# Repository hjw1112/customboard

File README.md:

# Customboard!

This is a custom built mechanical keyboard. Everything except switches and keycaps are custom built including pcb and case!

I always wanted to get a mechanical keyboard but It was to expensive to get. But, I learnt how to make simple macropad by hack club event "hackpad" and started working on this. Also, I liked the idea because everything was customizable including silkscreen on PCB and every behavior of keyboard.

You can work on the same project or benchmark this if you want to. I have all source file or link to source file of the project in this repo :)

### PCB

### Schematic

### Case

---
### BOM

# Custom Keyboard BOM (Bill of Materials)

| Component                    | Price (USD) | Price (EUR) | Source     |
|------------------------------|-------------|-------------|------------|
| Nice!nano compatible board   | $4.86       | €4.26       | Aliexpress |
| Kailh hotswap sockets        | $8.52       | €7.47       | Aliexpress |
| Akko V3 Pro Cream Switches   | $33.21      | €29.13      | Aliexpress |
| 0.91 inch OLED               | $1.01       | €0.89       | Aliexpress |
| TCA9555 expansion board      | $3.52       | €3.09       | Aliexpress |
| Stabilizers                  | $11.92      | €10.46      | Aliexpress |
| EC11 encoder                 | $5.07       | €4.45       | Aliexpress |
| 1N4148 Diodes                | $1.45       | €1.27       | Aliexpress |
| 0603 SMD 1000nF capacitor    | $1.36       | €1.19       | Aliexpress |
| 0603 SMD 4.7k resistor       | $1.12       | €0.98       | Aliexpress |
| M2.5 heatset insert          | $2.44       | €2.14       | Aliexpress |
| M2.5 screws                  | $5.48       | €4.81       | Aliexpress |
| Foam                         | $6.48       | €5.68       | Aliexpress |
| Keycaps                      | $16.89      | €14.82      | Aliexpress |
| Standoff                     | $3.23       | €2.83       | Aliexpress |
| Battery                      | $6.50       | €5.70       | Aliexpress |
| JST PH2.0 male connector     | $1.87       | €1.64       | Aliexpress |
| Cable                        | $11.92      | €10.46      | Aliexpress |
| PCB                          | $19.80      |             | JLC PCB    |

---

**Total: $146.65**

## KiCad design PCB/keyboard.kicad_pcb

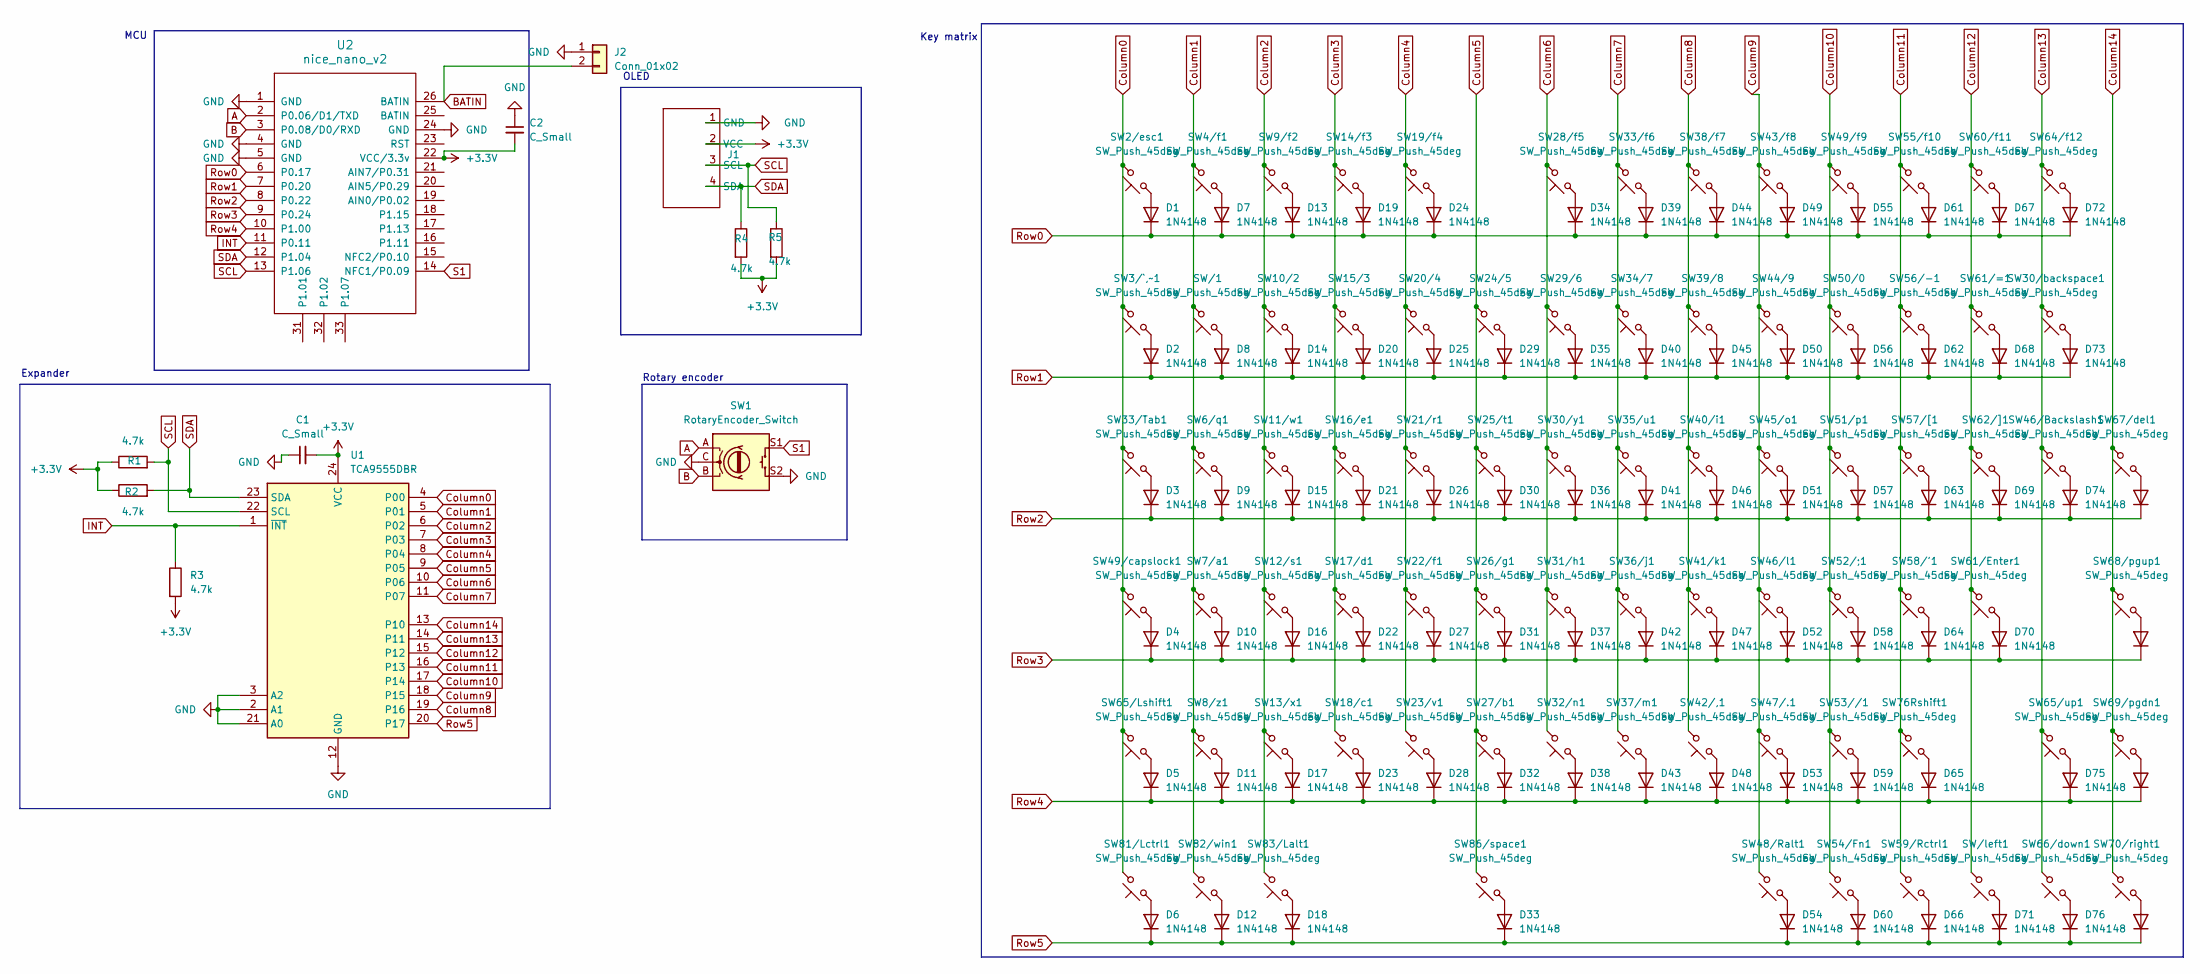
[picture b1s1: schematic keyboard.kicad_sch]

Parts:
C1, C2: C_Small; C_0603_1608Metric_Pad1.08x0.95mm_HandSolder
D1, D2, D3, D4, D5, D6, D7, D8, D9, D10, D11, D12, D13, D14, D15, D16, D17, D18, D19, D20, D21, D22, D23, D24, D25, D26, D27, D28, D29, D30, D31, D32, D33, D34, D35, D36, D37, D38, D39, D40, D41, D42, D43, D44, D45, D46, D47, D48, D49, D50, D51, D52, D53, D54, D55, D56, D57, D58, D59, D60, D61, D62, D63, D64, D65, D66, D67, D68, D69, D70, D71, D72, D73, D74, D75, D76, D77, D78, D79, D80: 1N4148; D_DO-35_SOD27_P7.62mm_Horizontal
J1: SSD1306-0.91-OLED-4pin-128x32
J2: Conn_01x02; JST_PH_S2B-PH-K_1x02_P2.00mm_Horizontal
R1, R2, R3, R4, R5: 4.7k; R_0603_1608Metric_Pad0.98x0.95mm_HandSolder
SW1: RotaryEncoder_Switch; RotaryEncoder_Alps_EC11E-Switch_Vertical_H20mm_MountingHoles
SW2/esc1, SW3/`,~1, SW4/f1, SW6/q1, SW7/a1, SW8/z1, SW9/f2, SW10/2, SW11/w1, SW12/s1, SW13/x1, SW14/f3, SW15/3, SW16/e1, SW17/d1, SW18/c1, SW19/f4, SW20/4, SW21/r1, SW22/f1, SW23/v1, SW24/5, SW25/t1, SW26/g1, SW27/b1, SW28/f5, SW29/6, SW30/y1, SW31/h1, SW32/n1, SW33/f6, SW34/7, SW35/u1, SW36/j1, SW37/m1, SW38/f7, SW39/8, SW40/i1, SW41/k1, SW42/,1, SW43/f8, SW44/9, SW45/o1, SW46/l1, SW47/.1, SW48/Ralt1, SW49/f9, SW50/0, SW51/p1, SW52/;1, SW53//1, SW54/Fn1, SW55/f10, SW56/-1, SW57/[1, SW58/'1, SW59/Rctrl1, SW60/f11, SW61/=1, SW62/]1, SW64/f12, SW65/up1, SW66/down1, SW67/del1, SW68/pgup1, SW69/pgdn1, SW70/right1: SW_Push_45deg; CherryMX_1.00u_KailhSocket
SW30/backspace1: SW_Push_45deg; CherryMX_2.00u_KailhSocket_StabWireBottom
SW33/Tab1, SW46/Backslash1: SW_Push_45deg; CherryMX_1.50u_KailhSocket
SW49/capslock1, SW76Rshift1: SW_Push_45deg; CherryMX_1.75u_KailhSocket
SW61/Enter1, SW65/Lshift1: SW_Push_45deg; CherryMX_2.25u_KailhSocket_StabWireBottom
SW81/Lctrl1, SW82/win1, SW83/Lalt1: SW_Push_45deg; CherryMX_1.25u_KailhSocket
SW86/space1: SW_Push_45deg; CherryMX_6.25u_KailhSocket_StabWireBottom
SW/1: SW_Push_45deg; CherryMX_1.00u_KailhSocket
SW/left1: SW_Push_45deg; CherryMX_1.00u_KailhSocket
U1: TCA9555DBR; SSOP-24_5.3x8.2mm_P0.65mm
U2: nice_nano_v2; nice nano v2 final

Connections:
+3.3V: C1.2, C2.2, J1.2 (VCC), R1.1, R2.1, R3.2, R4.2, R5.2, U1.24 (VCC), U2.22 (VCC/3.3v)
A: SW1.A, U2.2 (P0.06/D1/TXD)
B: SW1.B, U2.3 (P0.08/D0/RXD)
BATIN: J2.2, U2.26 (BATIN)
Column0: SW2/esc1.2, SW3/`,~1.2, SW33/Tab1.2, SW49/capslock1.2, SW65/Lshift1.2, SW81/Lctrl1.2, U1.4 (P00)
Column1: SW4/f1.2, SW6/q1.2, SW7/a1.2, SW8/z1.2, SW82/win1.2, SW/1.2, U1.5 (P01)
Column2: SW9/f2.2, SW10/2.2, SW11/w1.2, SW12/s1.2, SW13/x1.2, SW83/Lalt1.2, U1.6 (P02)
Column3: SW14/f3.2, SW15/3.2, SW16/e1.2, SW17/d1.2, SW18/c1.2, U1.7 (P03)
Column4: SW19/f4.2, SW20/4.2, SW21/r1.2, SW22/f1.2, SW23/v1.2, U1.8 (P04)
Column5: SW24/5.2, SW25/t1.2, SW26/g1.2, SW27/b1.2, SW86/space1.2, U1.9 (P05)
Column6: SW28/f5.2, SW29/6.2, SW30/y1.2, SW31/h1.2, SW32/n1.2, U1.10 (P06)
Column7: SW33/f6.2, SW34/7.2, SW35/u1.2, SW36/j1.2, SW37/m1.2, U1.11 (P07)
Column8: SW38/f7.2, SW39/8.2, SW40/i1.2, SW41/k1.2, SW42/,1.2, U1.19 (P16)
Column9: SW43/f8.2, SW44/9.2, SW45/o1.2, SW46/l1.2, SW47/.1.2, SW48/Ralt1.2, U1.18 (P15)
Column10: SW49/f9.2, SW50/0.2, SW51/p1.2, SW52/;1.2, SW53//1.2, SW54/Fn1.2, U1.17 (P14)
Column11: SW55/f10.2, SW56/-1.2, SW57/[1.2, SW58/'1.2, SW59/Rctrl1.2, SW76Rshift1.2, U1.16 (P13)
Column12: SW60/f11.2, SW61/=1.2, SW61/Enter1.2, SW62/]1.2, SW/left1.2, U1.15 (P12)
Column13: SW30/backspace1.2, SW46/Backslash1.2, SW64/f12.2, SW65/up1.2, SW66/down1.2, U1.14 (P11)
Column14: SW67/del1.2, SW68/pgup1.2, SW69/pgdn1.2, SW70/right1.2, U1.13 (P10)
GND: C1.1, C2.1, J1.1 (GND), J2.1, SW1.C, SW1.S2, U1.2 (A1), U1.3 (A2), U1.12 (GND), U1.21 (A0), U2.1 (GND), U2.4 (GND), U2.5 (GND), U2.24 (GND)
INT: R3.1, U1.1 (~INT), U2.11 (P0.11)
unnamed: D1.2 (A), SW2/esc1.1
unnamed: D2.2 (A), SW3/`,~1.1
unnamed: D3.2 (A), SW33/Tab1.1
unnamed: D4.2 (A), SW49/capslock1.1
unnamed: D5.2 (A), SW65/Lshift1.1
unnamed: D6.2 (A), SW81/Lctrl1.1
unnamed: D7.2 (A), SW4/f1.1
unnamed: D8.2 (A), SW/1.1
unnamed: D9.2 (A), SW6/q1.1
unnamed: D10.2 (A), SW7/a1.1
unnamed: D11.2 (A), SW8/z1.1
unnamed: D12.2 (A), SW82/win1.1
unnamed: D13.2 (A), SW9/f2.1
unnamed: D14.2 (A), SW10/2.1
unnamed: D15.2 (A), SW11/w1.1
unnamed: D16.2 (A), SW12/s1.1
unnamed: D17.2 (A), SW13/x1.1
unnamed: D18.2 (A), SW83/Lalt1.1
unnamed: D19.2 (A), SW14/f3.1
unnamed: D20.2 (A), SW15/3.1
unnamed: D21.2 (A), SW16/e1.1
unnamed: D22.2 (A), SW17/d1.1
unnamed: D23.2 (A), SW18/c1.1
unnamed: D24.2 (A), SW19/f4.1
unnamed: D25.2 (A), SW20/4.1
unnamed: D26.2 (A), SW21/r1.1
unnamed: D27.2 (A), SW22/f1.1
unnamed: D28.2 (A), SW23/v1.1
unnamed: D29.2 (A), SW24/5.1
unnamed: D30.2 (A), SW25/t1.1
unnamed: D31.2 (A), SW26/g1.1
unnamed: D32.2 (A), SW27/b1.1
unnamed: D33.2 (A), SW86/space1.1
unnamed: D34.2 (A), SW28/f5.1
unnamed: D35.2 (A), SW29/6.1
unnamed: D36.2 (A), SW30/y1.1
unnamed: D37.2 (A), SW31/h1.1
unnamed: D38.2 (A), SW32/n1.1
unnamed: D39.2 (A), SW33/f6.1
unnamed: D40.2 (A), SW34/7.1
unnamed: D41.2 (A), SW35/u1.1
unnamed: D42.2 (A), SW36/j1.1
unnamed: D43.2 (A), SW37/m1.1
unnamed: D44.2 (A), SW38/f7.1
unnamed: D45.2 (A), SW39/8.1
unnamed: D46.2 (A), SW40/i1.1
unnamed: D47.2 (A), SW41/k1.1
unnamed: D48.2 (A), SW42/,1.1
unnamed: D49.2 (A), SW43/f8.1
unnamed: D50.2 (A), SW44/9.1
unnamed: D51.2 (A), SW45/o1.1
unnamed: D52.2 (A), SW46/l1.1
unnamed: D53.2 (A), SW47/.1.1
unnamed: D54.2 (A), SW48/Ralt1.1
unnamed: D55.2 (A), SW49/f9.1
unnamed: D56.2 (A), SW50/0.1
unnamed: D57.2 (A), SW51/p1.1
unnamed: D58.2 (A), SW52/;1.1
unnamed: D59.2 (A), SW53//1.1
unnamed: D60.2 (A), SW54/Fn1.1
unnamed: D61.2 (A), SW55/f10.1
unnamed: D62.2 (A), SW56/-1.1
unnamed: D63.2 (A), SW57/[1.1
unnamed: D64.2 (A), SW58/'1.1
unnamed: D65.2 (A), SW76Rshift1.1
unnamed: D66.2 (A), SW59/Rctrl1.1
unnamed: D67.2 (A), SW60/f11.1
unnamed: D68.2 (A), SW61/=1.1
unnamed: D69.2 (A), SW62/]1.1
unnamed: D70.2 (A), SW61/Enter1.1
unnamed: D71.2 (A), SW/left1.1
unnamed: D72.2 (A), SW64/f12.1
unnamed: D73.2 (A), SW30/backspace1.1
unnamed: D74.2 (A), SW46/Backslash1.1
unnamed: D75.2 (A), SW65/up1.1
unnamed: D76.2 (A), SW66/down1.1
unnamed: D77.2 (A), SW67/del1.1
unnamed: D78.2 (A), SW68/pgup1.1
unnamed: D79.2 (A), SW69/pgdn1.1
unnamed: D80.2 (A), SW70/right1.1
Row0: D1.1 (K), D7.1 (K), D13.1 (K), D19.1 (K), D24.1 (K), D34.1 (K), D39.1 (K), D44.1 (K), D49.1 (K), D55.1 (K), D61.1 (K), D67.1 (K), D72.1 (K), U2.6 (P0.17)
Row1: D2.1 (K), D8.1 (K), D14.1 (K), D20.1 (K), D25.1 (K), D29.1 (K), D35.1 (K), D40.1 (K), D45.1 (K), D50.1 (K), D56.1 (K), D62.1 (K), D68.1 (K), D73.1 (K), U2.7 (P0.20)
Row2: D3.1 (K), D9.1 (K), D15.1 (K), D21.1 (K), D26.1 (K), D30.1 (K), D36.1 (K), D41.1 (K), D46.1 (K), D51.1 (K), D57.1 (K), D63.1 (K), D69.1 (K), D74.1 (K), D77.1 (K), U2.8 (P0.22)
Row3: D4.1 (K), D10.1 (K), D16.1 (K), D22.1 (K), D27.1 (K), D31.1 (K), D37.1 (K), D42.1 (K), D47.1 (K), D52.1 (K), D58.1 (K), D64.1 (K), D70.1 (K), D78.1 (K), U2.9 (P0.24)
Row4: D5.1 (K), D11.1 (K), D17.1 (K), D23.1 (K), D28.1 (K), D32.1 (K), D38.1 (K), D43.1 (K), D48.1 (K), D53.1 (K), D59.1 (K), D65.1 (K), D75.1 (K), D79.1 (K), U2.10 (P1.00)
Row5: D6.1 (K), D12.1 (K), D18.1 (K), D33.1 (K), D54.1 (K), D60.1 (K), D66.1 (K), D71.1 (K), D76.1 (K), D80.1 (K), U1.20 (P17)
S1: SW1.S1, U2.14 (NFC1/P0.09)
SCL: J1.3 (SCL), R1.2, R5.1, U1.22 (SCL), U2.13 (P1.06)
SDA: J1.4 (SDA), R2.2, R4.1, U1.23 (SDA), U2.12 (P1.04)

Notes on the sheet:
Key matrix
Rotary encoder
MCU
OLED
Expander

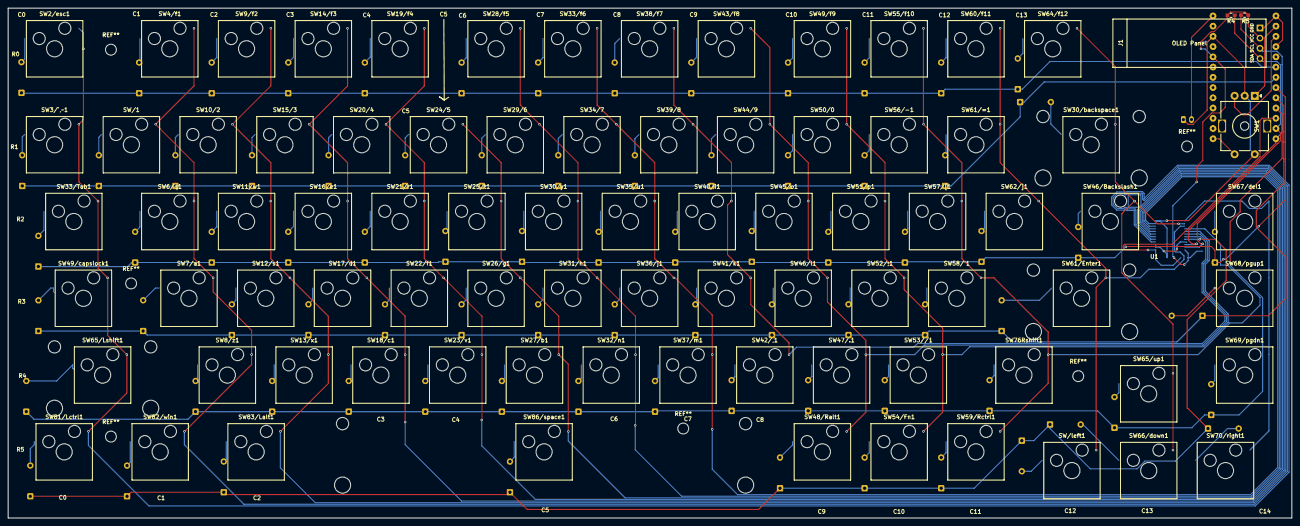
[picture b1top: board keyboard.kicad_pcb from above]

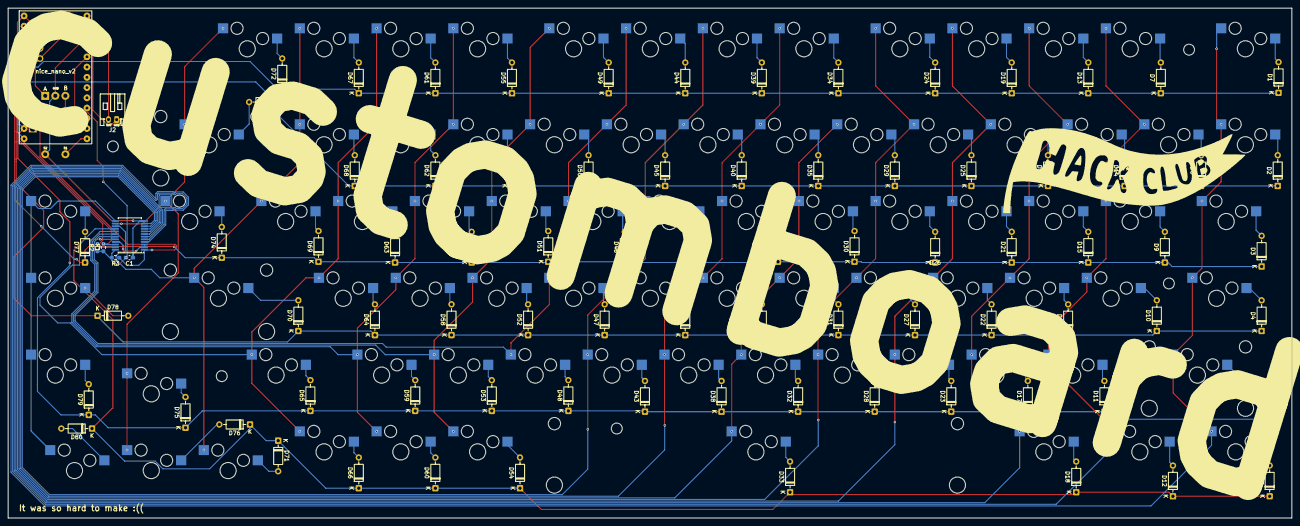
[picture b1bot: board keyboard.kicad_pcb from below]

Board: 2 copper layers, 318.5 x 126.5 mm, 172 parts (88 on the bottom side), 110 nets.

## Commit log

2025-06-01 init
2025-06-01 added project details to journal.md
2025-06-01 project detail edit
2025-06-01 6/1 keymatrix
2025-06-02 6/1, 6/2 update
2025-06-04 6/3, 6/4
2025-06-08 6/5 ~ 6/8
2025-06-08 added success pic :)))
2025-06-08 Updated CAD step files. i forgot them
2025-06-11 Update JOURNAL.md, need more update
